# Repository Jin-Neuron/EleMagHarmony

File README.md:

# Ele Mag Harmony

## Requirement

MPU (board) : STM32F303K8T6 (Nucleo-32)

Driver : EleMagDriver v3.0

Band Instrument (Part) : 
 - Stepping Motor (Melody) 
 - Solenoid (Guitar)
 - Floppy Disc Drive (Base)
 - Relay (Drum)

Player : EleMagPlayer v3.0

Power : 12V 3A AC Adapter

Guitar：ElectricGuitar with Solenoid Mount

GuitarAmplifier：Basic

## Installation

### Hardware

EleMagDriver、Nucleoボード、電源、そしてバンドの構成楽器各種を準備します。

ギターにはアンプを接続し、ソレノイドマウントをつけてソレノイドを取り付けます。

ソレノイドマウントはHardware -> Guitar　内にstlファイルをアップロードしておりますので、そちらを活用してください。

EleMagDriverは基板のガーバーをアップロードしているので活用してください。v3.0ではオーディオビジュアライザー機能も搭載しています。

EleMag Driverの接続は基板に書かれている通りです。フロッピードライブ以外はxhのコネクタで接続する必要があります。

フロッピードライブは2.5mmピッチのQIのコネクタで電源を接続し、信号はFDDの接続に標準的な34ピンのMILコネクタを使用します。

### Software

Windows10以上（推奨）PCにEleMagPlayerをインストールします。

EleMagPlayerの基本動作はPlayerフォルダ内のreadmeを参照してください。

# Useage

上記の手順により、Playerでの再生が可能になります。Playerの再生方法に関してはPlayerのreadmeを参照してください。

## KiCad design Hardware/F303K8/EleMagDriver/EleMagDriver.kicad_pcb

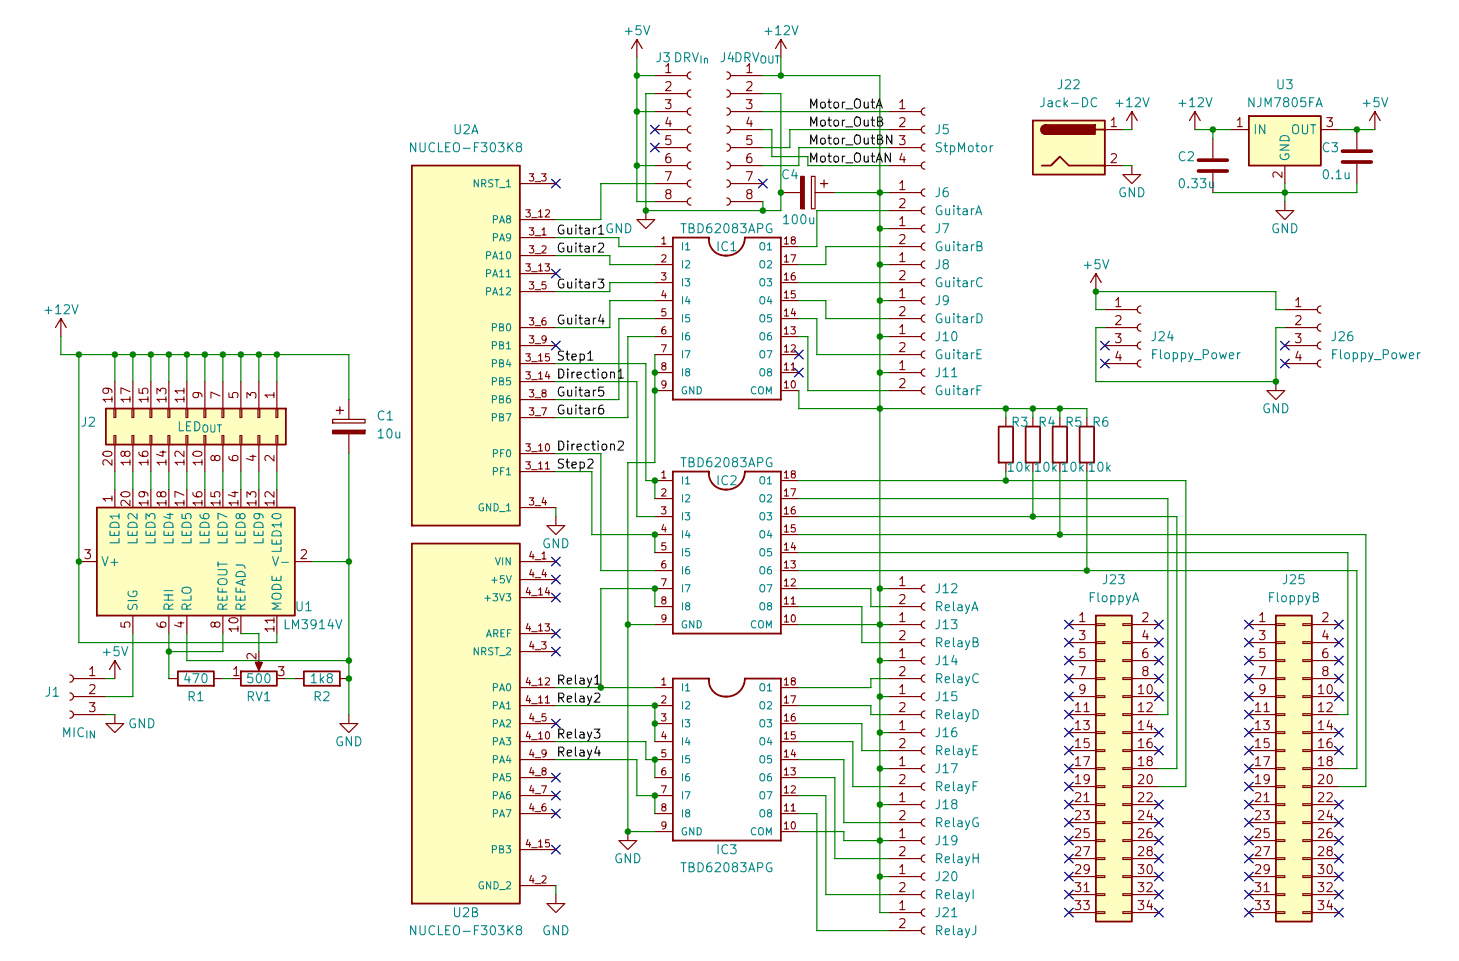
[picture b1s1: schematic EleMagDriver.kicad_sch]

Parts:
C1: 10u; CP_Radial_D5.0mm_P2.00mm
C2: 0.33u; C_Disc_D4.7mm_W2.5mm_P5.00mm
C3: 0.1u; C_Disc_D4.7mm_W2.5mm_P5.00mm
C4: 100u; CP_Radial_D6.3mm_P2.50mm
IC1, IC2, IC3: TBD62083APG; DIP-18_W7.62mm
J1: MIC_{IN}; PinSocket_1x03_P2.54mm_Vertical
J2: LED_{OUT}; PinHeader_2x10_P2.54mm_Vertical
J3: DRV_{In}; PinSocket_1x08_P2.54mm_Vertical
J4: DRV_{OUT}; PinSocket_1x08_P2.54mm_Vertical
J5: StpMotor; JST_XH_S4B-XH-A_1x04_P2.50mm_Horizontal
J6: GuitarA; JST_XH_S2B-XH-A_1x02_P2.50mm_Horizontal
J7: GuitarB; JST_XH_S2B-XH-A_1x02_P2.50mm_Horizontal
J8: GuitarC; JST_XH_S2B-XH-A_1x02_P2.50mm_Horizontal
J9: GuitarD; JST_XH_S2B-XH-A_1x02_P2.50mm_Horizontal
J10: GuitarE; JST_XH_S2B-XH-A_1x02_P2.50mm_Horizontal
J11: GuitarF; JST_XH_S2B-XH-A_1x02_P2.50mm_Horizontal
J12: RelayA; JST_XH_B2B-XH-A_1x02_P2.50mm_Vertical
J13: RelayB; JST_XH_B2B-XH-A_1x02_P2.50mm_Vertical
J14: RelayC; JST_XH_B2B-XH-A_1x02_P2.50mm_Vertical
J15: RelayD; JST_XH_B2B-XH-A_1x02_P2.50mm_Vertical
J16: RelayE; JST_XH_B2B-XH-A_1x02_P2.50mm_Vertical
J17: RelayF; JST_XH_B2B-XH-A_1x02_P2.50mm_Vertical
J18: RelayG; JST_XH_B2B-XH-A_1x02_P2.50mm_Vertical
J19: RelayH; JST_XH_B2B-XH-A_1x02_P2.50mm_Vertical
J20: RelayI; JST_XH_B2B-XH-A_1x02_P2.50mm_Vertical
J21: RelayJ; JST_XH_B2B-XH-A_1x02_P2.50mm_Vertical
J22: Jack-DC; BarrelJack_Horizontal
J23: FloppyA; SHDR34W70P254_2X17_5050X820X900P
J24, J26: Floppy_Power; PinHeader_1x04_P2.54mm_Horizontal
J25: FloppyB; SHDR34W70P254_2X17_5050X820X900P
R1: 470; R_Axial_DIN0207_L6.3mm_D2.5mm_P10.16mm_Horizontal
R2: 1k8; R_Axial_DIN0207_L6.3mm_D2.5mm_P10.16mm_Horizontal
R3, R4, R5, R6: 10k; R_Axial_DIN0207_L6.3mm_D2.5mm_P10.16mm_Horizontal
RV1: 500; Potentiometer_Bourns_3386P_Vertical
U1: LM3914V; PLCC-20
U2: NUCLEO-F303K8; MODULE_NUCLEO-F303K8; PARTREV 5
U3: NJM7805FA; TO-220-3_Vertical

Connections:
+5V: C3.1, J1.1, J3.1, J3.3, J3.6, J3.8, J24.1, J26.1, U3.3 (OUT)
+12V: C1.1, C2.1, C4.1, IC1.10 (COM), IC2.10 (COM), IC3.10 (COM), J2.1, J2.3, J2.5, J2.7, J2.9, J2.11, J2.13, J2.15, J2.17, J2.19, J4.1, J6.1, J7.1, J8.1, J9.1, J10.1, J11.1, J12.1, J13.1, J14.1, J15.1, J16.1, J17.1, J18.1, J19.1, J20.1, J21.1, J22.1, R3.1, R4.1, R5.1, R6.1, U1.3 (V+), U1.11 (MODE), U3.1 (IN)
/Direction1: IC2.3 (I3), U2.3_14 (PB5)
/Direction2: IC2.6 (I6), U2.3_10 (PF0)
/Guitar1: IC1.1 (I1), U2.3_1 (PA9)
/Guitar2: IC1.2 (I2), U2.3_2 (PA10)
/Guitar3: IC1.3 (I3), U2.3_5 (PA12)
/Guitar4: IC1.4 (I4), U2.3_6 (PB0)
/Guitar5: IC1.5 (I5), U2.3_8 (PB6)
/Guitar6: IC1.6 (I6), U2.3_7 (PB7)
/Motor_OutA: J4.3, J5.1
/Motor_OutAN: J4.4, J5.4
/Motor_OutB: J4.5, J5.2
/Motor_OutBN: J4.6, J5.3
/Relay1: IC2.7 (I7), IC2.8 (I8), IC3.1 (I1), U2.4_12 (PA0)
/Relay2: IC3.2 (I2), IC3.3 (I3), IC3.4 (I4), U2.4_11 (PA1)
/Relay3: IC3.5 (I5), IC3.6 (I6), U2.4_10 (PA3)
/Relay4: IC3.7 (I7), IC3.8 (I8), U2.4_9 (PA4)
/Step1: IC2.1 (I1), IC2.2 (I2), U2.3_15 (PB4)
/Step2: IC2.4 (I4), IC2.5 (I5), U2.3_11 (PF1)
GND: C1.2, C2.2, C3.2, C4.2, IC1.7 (I7), IC1.8 (I8), IC1.9 (GND), IC2.9 (GND), IC3.9 (GND), J1.3, J3.2, J4.2, J4.8, J22.2, J24.2, J26.2, R2.2, U1.2 (V-), U1.4 (RLO), U2.3_4 (GND_1), U2.4_2 (GND_2), U3.2 (GND)
unnamed: IC1.18 (O1), J6.2
unnamed: IC1.17 (O2), J7.2
unnamed: IC1.16 (O3), J8.2
unnamed: IC1.15 (O4), J9.2
unnamed: IC1.14 (O5), J10.2
unnamed: IC1.13 (O6), J11.2
unnamed: IC2.18 (O1), J23.20, R3.2
unnamed: IC2.17 (O2), J23.12
unnamed: IC2.16 (O3), J23.18, R4.2
unnamed: IC2.15 (O4), J25.20, R5.2
unnamed: IC2.14 (O5), J25.12
unnamed: IC2.13 (O6), J25.18, R6.2
unnamed: IC2.12 (O7), J12.2
unnamed: IC2.11 (O8), J13.2
unnamed: IC3.18 (O1), J14.2
unnamed: IC3.17 (O2), J15.2
unnamed: IC3.16 (O3), J16.2
unnamed: IC3.15 (O4), J17.2
unnamed: IC3.14 (O5), J18.2
unnamed: IC3.13 (O6), J19.2
unnamed: IC3.12 (O7), J20.2
unnamed: IC3.11 (O8), J21.2
unnamed: J1.2, U1.5 (SIG)
unnamed: J2.2, U1.12 (LED10)
unnamed: J2.4, U1.13 (LED9)
unnamed: J2.6, U1.14 (LED8)
unnamed: J2.8, U1.15 (LED7)
unnamed: J2.10, U1.16 (LED6)
unnamed: J2.12, U1.17 (LED5)
unnamed: J2.14, U1.18 (LED4)
unnamed: J2.16, U1.19 (LED3)
unnamed: J2.18, U1.20 (LED2)
unnamed: J2.20, U1.1 (LED1)
unnamed: J3.7, U2.3_12 (PA8)
unnamed: R1.2, RV1.1
unnamed: R2.1, RV1.3
unnamed: RV1.2, U1.10 (REFADJ)
unnamed: R1.1, U1.6 (RHI), U1.8 (REFOUT)

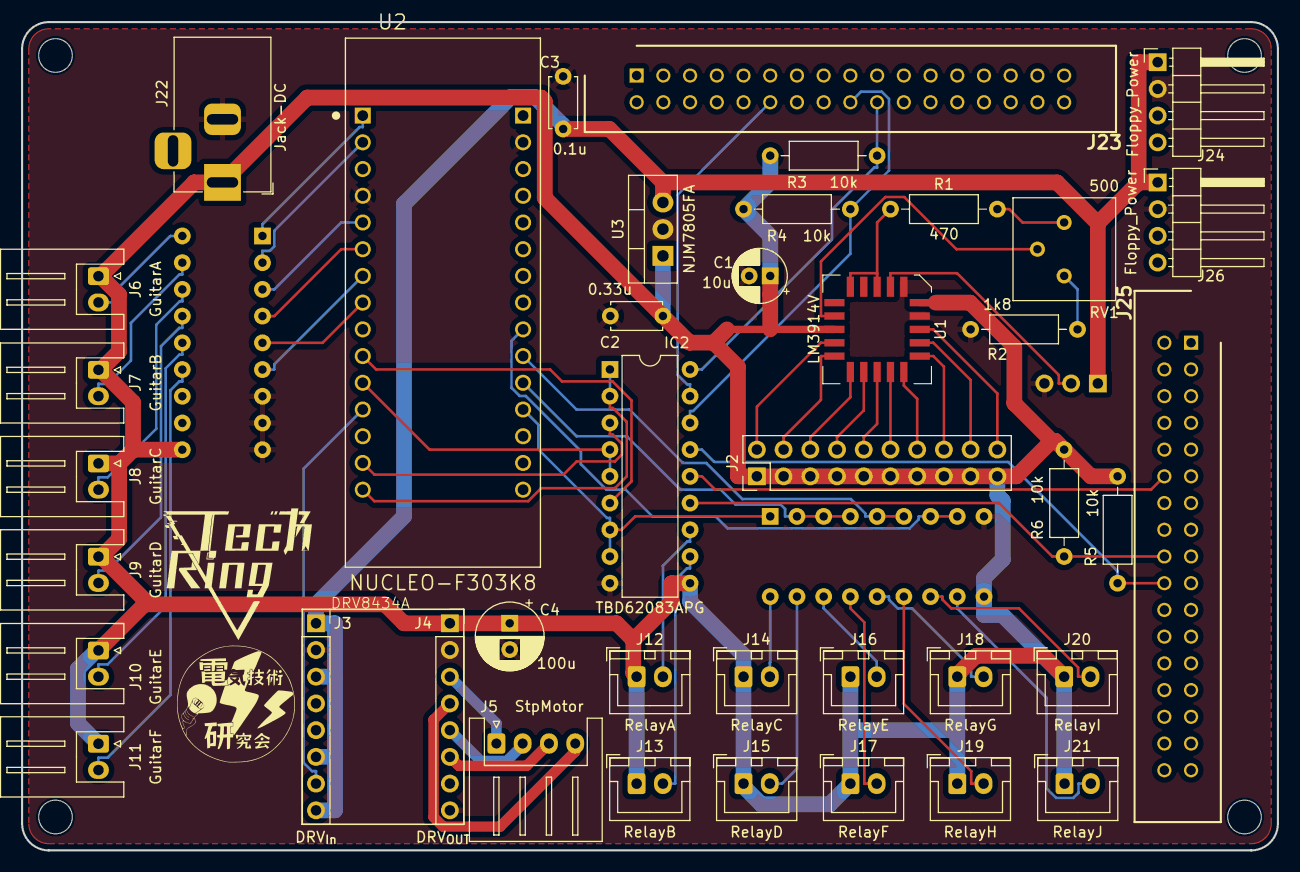
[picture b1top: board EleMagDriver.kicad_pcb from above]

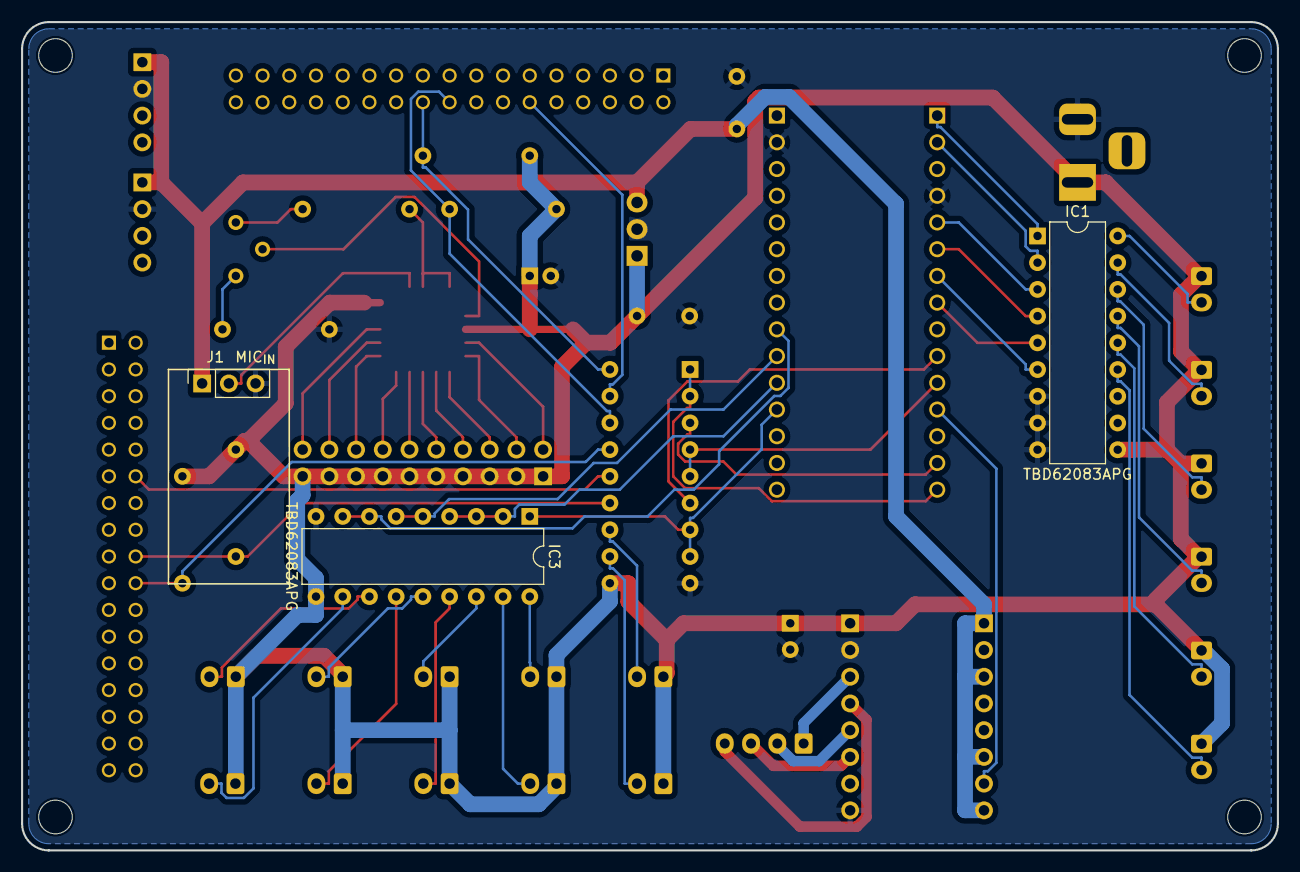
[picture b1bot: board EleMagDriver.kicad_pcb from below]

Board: 2 copper layers, 119.4 x 78.7 mm, 45 parts (3 on the bottom side), 59 nets.

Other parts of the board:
G0: LOGO; TechRing
G1: LOGO; Denken

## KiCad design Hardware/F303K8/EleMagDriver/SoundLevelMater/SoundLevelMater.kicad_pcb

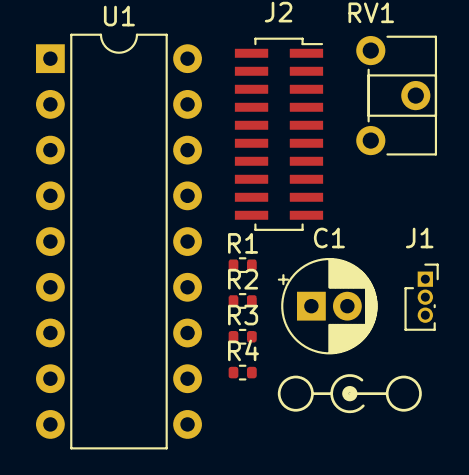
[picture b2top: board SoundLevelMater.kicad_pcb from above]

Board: 2 copper layers, 10 parts (0 on the bottom side), 8 nets, no tracks yet.

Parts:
C1: C_Polarized; CP_Radial_D5.0mm_P2.00mm
J1: Conn_01x03_Socket; PinSocket_1x03_P1.00mm_Vertical
J2: Conn_02x10_Row_Letter_Last; PinSocket_2x10_P1.00mm_Vertical_SMD
J3: Barrel_Jack; Symbol_Barrel_Polarity
R1, R2, R3, R4: R; R_0402_1005Metric
RV1: R_Potentiometer; Potentiometer_ACP_CA6-H2,5_Horizontal
U1: LM3914N; DIP-18_W7.62mm

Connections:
+5V: C1.1, J1.1, U1.3 (V+), U1.9 (MODE)
GND: C1.2, J1.2, R3.2, R4.2, U1.2 (V-), U1.4 (RLO)
unnamed: J1.3, R2.1
unnamed: R1.2, RV1.1
unnamed: R3.1, RV1.3
unnamed: RV1.2, U1.8 (REFADJ)
unnamed: R1.1, U1.6 (RHI), U1.7 (REFOUT)
unnamed: R2.2, R4.1, U1.5 (SIG)

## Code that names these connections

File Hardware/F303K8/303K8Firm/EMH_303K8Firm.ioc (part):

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Mcu.Name=STM32F303K(6-8)Tx
Mcu.Package=LQFP32
Mcu.UserName=STM32F303K8Tx
PA0.GPIOParameters=GPIO_Label
PA0.GPIO_Label=Relay1
PA0.Signal=GPIO_Output
PA1.GPIOParameters=GPIO_Label
PA1.GPIO_Label=Relay2
PA1.Signal=GPIO_Output
PA10.GPIOParameters=GPIO_Label
PA10.GPIO_Label=Guitar2
PA10.Signal=GPIO_Output
PA12.GPIOParameters=GPIO_Label
PA12.GPIO_Label=Guitar3
PA12.Signal=GPIO_Output
PA13.GPIOParameters=GPIO_Label
PA13.GPIO_Label=SWDIO
PA13.Mode=Serial_Wire
PA13.Signal=SYS_JTMS-SWDIO
PA14.GPIOParameters=GPIO_Label
PA14.GPIO_Label=SWCLK
PA14.Mode=Serial_Wire
PA14.Signal=SYS_JTCK-SWCLK
PA15.GPIOParameters=GPIO_Label
PA15.GPIO_Label=VCP_RX
PA15.Mode=Asynchronous
PA15.Signal=USART2_RX
PA2.GPIOParameters=GPIO_Label
PA2.GPIO_Label=VCP_TX
PA2.Mode=Asynchronous
PA2.Signal=USART2_TX
PA3.GPIOParameters=GPIO_Label
PA3.GPIO_Label=Relay3
PA3.Signal=GPIO_Output
PA4.GPIOParameters=GPIO_Label
PA4.GPIO_Label=Relay4
PA4.Signal=GPIO_Output
PA8.GPIOParameters=GPIO_Label
PA8.GPIO_Label=StpMotor
PA8.Signal=S_TIM1_CH1
PA9.GPIOParameters=GPIO_Label
PA9.GPIO_Label=Guitar1
PA9.Signal=GPIO_Output
PB0.GPIOParameters=GPIO_Label
PB0.GPIO_Label=Guitar4
PB0.Signal=GPIO_Output
PB4.GPIOParameters=GPIO_Label
PB4.GPIO_Label=Step1
PB4.Signal=GPIO_Output
PB5.GPIOParameters=GPIO_Label
PB5.GPIO_Label=Direction1
PB5.Signal=GPIO_Output
PB6.GPIOParameters=GPIO_Label
PB6.GPIO_Label=Guitar5
PB6.Signal=GPIO_Output
PB7.GPIOParameters=GPIO_Label
PB7.GPIO_Label=Guitar6
PB7.Signal=GPIO_Output
PF0\ /\ OSC_IN.GPIOParameters=GPIO_Label
PF0\ /\ OSC_IN.GPIO_Label=Direction2
PF0\ /\ OSC_IN.Signal=GPIO_Output
PF1\ /\ OSC_OUT.GPIOParameters=GPIO_Label
PF1\ /\ OSC_OUT.GPIO_Label=Step2
PF1\ /\ OSC_OUT.Signal=GPIO_Output
RCC.HSEPLLFreq_Value=8000000
RCC.HSE_VALUE=8000000
RCC.SYSCLKFreq_VALUE=64000000
RCC.SYSCLKSourceVirtual=RCC_SYSCLKSOURCE_PLLCLK
board=NUCLEO-F303K8
boardIOC=true

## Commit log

2020-04-07 非同期処理等
2020-04-16 v1 Commit
2020-10-02 ベータ版
2020-10-03 Test
2020-10-05 Beta
2020-10-05 ベータ版v3.1
2021-04-11 タイマーの誤差修正
2021-04-14 TrackBarの追加
2021-04-17 バイナリ送信
2021-04-17 バイナリ送信完成版
2021-04-17 不具合修正
2021-06-28 'テスト'
2021-06-28 aaaa
    aa
2021-06-28 asdsda
    dsasdads
2022-10-07 '修正'
2022-11-16 ignoreの修正
2023-02-21 add Player
2023-02-21 Change
2023-02-21 add Stm32Firm
2023-02-22 add timer and uart
2023-02-23 reset
2023-02-23 resetcachw
2023-02-23 change .gitignore
2023-02-23 remove
2023-02-23 add Relay, Floppy, Solenoid
2023-02-23 add picture
2023-02-23 edit comment
2023-02-23 add Pinout
2023-02-24 change UI and project name
2023-02-25 add StatusBar
2023-02-28 add demoPlaying function, LogFilter, and the others
2023-03-01 add Function and SettingMenu and Form
2023-03-02 Edit part
2023-03-02 Add F303Firm
2023-03-02 add .gitignore
2023-03-02 Edig floppyControl
2023-03-02 Upgrade Timer and change form
2023-03-03 serial
2023-03-04 update timer and midi play
2023-03-04 prototype
2023-03-06 prototype v2
2023-03-06 prototype v2.1
2023-03-07 serial update
2023-03-07 update drum part
2023-03-08 ui update and bug fixes
2023-03-09 adjust
2023-04-01 Add Stepping Motor
2023-04-01 change Pin and Player UI
2023-04-01 edit circuit
2023-04-01 add dcdc converter
2023-04-01 change folder structure
2023-04-01 delete
2023-04-05 update Timer and bug fix
2023-04-05 bug fix
2023-04-09 add cad data
2023-04-09 gitignore
2023-04-18 add Garber
2023-04-18 edit some files
2023-04-28 edit
2023-08-28 add SoundLevelMater
2023-09-30 add guitar and more
2023-10-01 substrate add guitar and more
2023-10-01 fix tempo bug
2023-10-01 adjustment
2023-10-01 remove deveiceSetting and apply guitar note
2023-10-02 apply player to guitar
2023-10-02 fix bug
2023-10-03 change speed
2023-10-03 change stepping motor line
2023-10-03 add Mute and change max and min size
2023-10-04 add solenoid mount of guitar
2023-11-09 add readme
2023-11-09 add pic
